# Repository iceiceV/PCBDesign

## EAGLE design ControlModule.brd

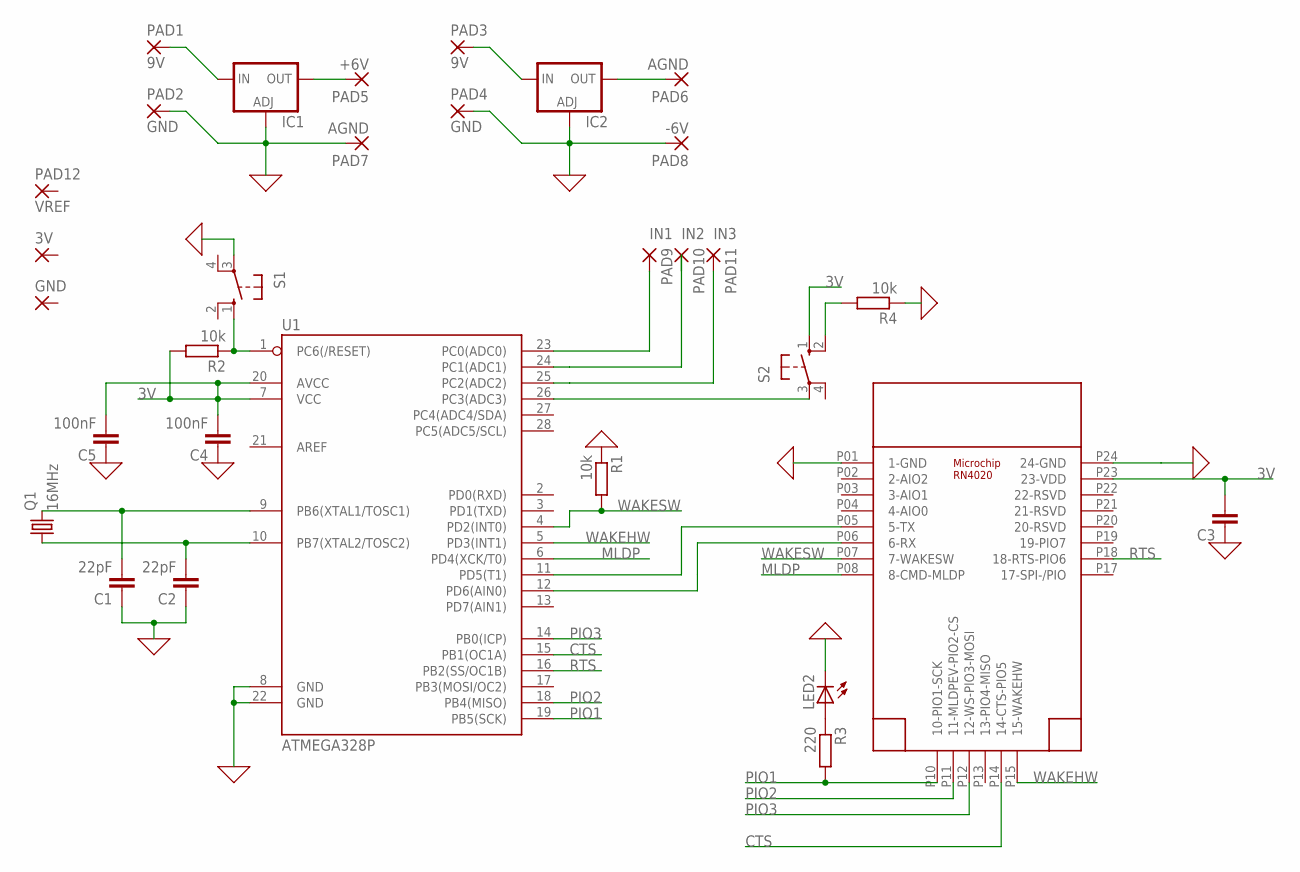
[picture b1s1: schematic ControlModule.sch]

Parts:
3V: 2,54/1,1
C1, C2: 22pF; C0603
C3: C-EUC0603; C0603
C4, C5: 100nF; C0603
GND: 2,54/1,1
IC1, IC2: LM138-TL; TO220L1
LED2: LEDCHIPLED_0603; CHIPLED_0603
PAD1, PAD3: 9V; 2,54/1,1
PAD2, PAD4: GND; 2,54/1,1
PAD5: +6V; 2,54/1,1
PAD6, PAD7: AGND; 2,54/1,1
PAD8: -6V; 2,54/1,1
PAD9, PAD10, PAD11: 2,54/1,1
PAD12: VREF; 2,54/1,1
Q1: 16MHz; HC49/S
R1, R2, R4: 10k; R0805
R3: 220; R0805
S1, S2: 10-XX; B3F-10XX
U1: ATMEGA328P; DIP28
U$1: RN4020; RN4020SMD

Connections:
0: C1.1, C2.1, C3.1, C4.1, C5.1, IC1.1 (ADJ), IC2.1 (ADJ), LED2.C, PAD2.1, PAD4.1, PAD7.1, PAD8.1, R1.1, R4.1, S1.3, U1.8 (GND), U1.22 (GND), U$1.P01 (1-GND), U$1.P24 (24-GND)
3V: C3.2, C4.2, C5.2, R2.2, S2.1 (S), U1.7 (VCC), U1.20 (AVCC), U$1.P23 (23-VDD)
9V: IC1.3 (IN), PAD1.1
CTS: U1.15 (PB1(OC1A)), U$1.P14 (14-CTS-PIO5)
IN1: PAD9.1, U1.23 (PC0(ADC0))
IN2: PAD10.1, U1.24 (PC1(ADC1))
IN3: PAD11.1, U1.25 (PC2(ADC2))
MLDP: U1.6 (PD4(XCK/T0)), U$1.P08 (8-CMD-MLDP)
unnamed: U1.12 (PD6(AIN0)), U$1.P06 (6-RX)
unnamed: U1.11 (PD5(T1)), U$1.P05 (5-TX)
unnamed: S2.3, U1.26 (PC3(ADC3))
unnamed: C1.2, Q1.2, U1.9 (PB6(XTAL1/TOSC1))
unnamed: IC2.3 (IN), PAD3.1
unnamed: IC1.2 (OUT), PAD5.1
unnamed: C2.2, Q1.1, U1.10 (PB7(XTAL2/TOSC2))
unnamed: IC2.2 (OUT), PAD6.1
unnamed: R2.1, S1.1 (S), U1.1 (PC6(/RESET))
unnamed: LED2.A, R3.1
unnamed: R4.2, S2.2 (S1)
PIO1: R3.2, U1.19 (PB5(SCK)), U$1.P10 (10-PIO1-SCK)
PIO2: U1.18 (PB4(MISO)), U$1.P11 (11-MLDPEV-PIO2-CS)
PIO3: U1.14 (PB0(ICP)), U$1.P12 (12-WS-PIO3-MOSI)
RTS: U1.16 (PB2(SS/OC1B)), U$1.P18 (18-RTS-PIO6)
WAKEHW: U1.5 (PD3(INT1)), U$1.P15 (15-WAKEHW)
WAKESW: R1.2, U1.4 (PD2(INT0)), U$1.P07 (7-WAKESW)

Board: 2 copper layers, 31 parts (0 on the bottom side), 25 nets, no tracks yet.

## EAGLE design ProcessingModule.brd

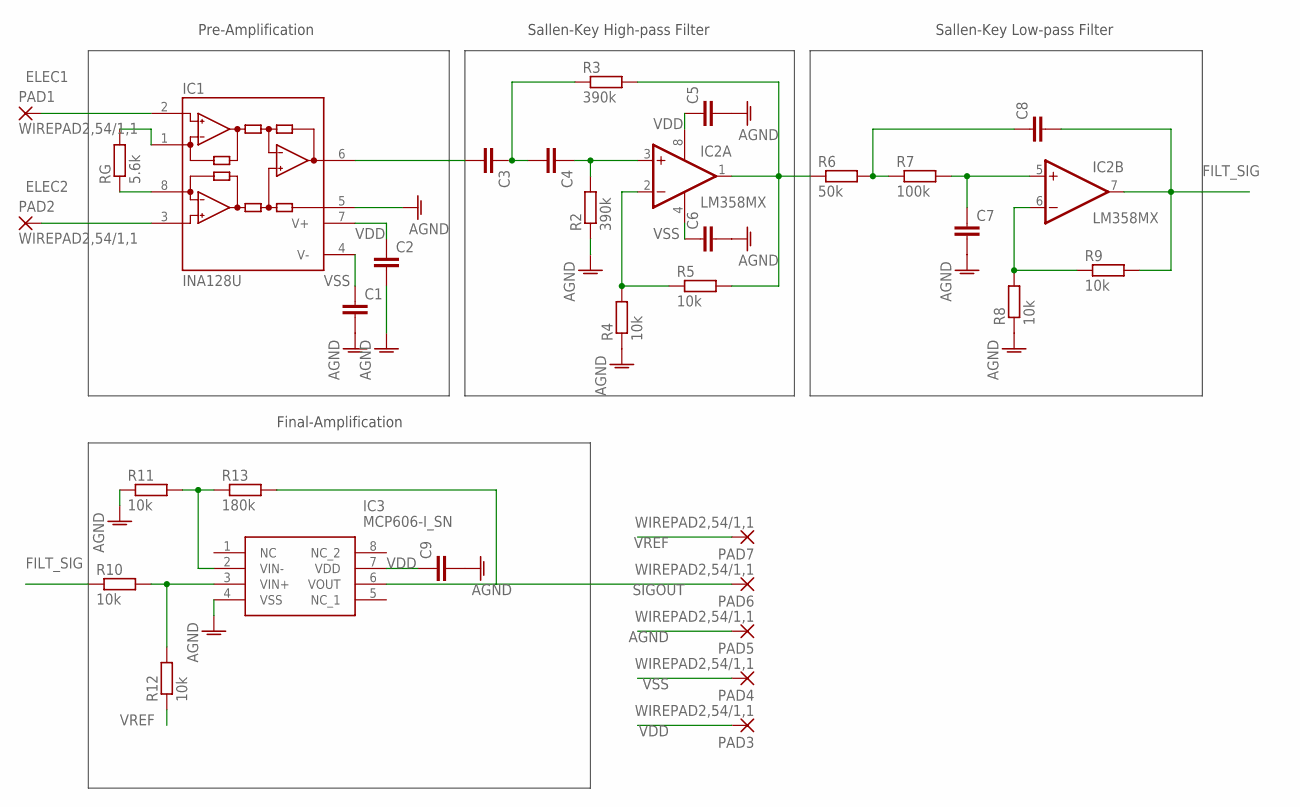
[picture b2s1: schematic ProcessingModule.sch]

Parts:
C1, C2, C3, C4, C5, C6, C7, C8, C9: C-EUC0603; C0603
IC1: INA128U; SO08
IC2: LM358MX; SO08
IC3: MCP606-I_SN; SOIC127P600X175-8N
PAD1, PAD2, PAD3, PAD4, PAD5, PAD6, PAD7: WIREPAD2,54/1,1; 2,54/1,1
R2, R3: 390k; R0805
R4, R5, R8, R9, R10, R11, R12: 10k; R0805
R6: 50k; R0805
R7: 100k; R0805
R13: 180k; R0805
RG: 5.6k; R0805

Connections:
AGND: C1.2, C2.2, C5.2, C6.2, C7.2, C9.2, IC1.5 (REF), IC3.4 (VSS), PAD5.1, R2.1, R4.1, R8.1, R11.1
ELEC1: IC1.2 (-IN), PAD1.1
ELEC2: IC1.3 (+IN), PAD2.1
FILT_SIG: C8.2, IC2.7 (OUT), R9.2, R10.1
unnamed: IC1.1 (RG), RG.2
unnamed: IC1.8 (RG), RG.1
unnamed: IC2.2 (-IN), R4.2, R5.1
unnamed 7: IC2.1 (OUT), R3.2, R5.2, R6.1; also elsewhere on the board
unnamed: C4.1, IC2.3 (+IN), R2.2
unnamed: C3.1, C4.2, R3.1
unnamed: C3.2, IC1.6 (OUT)
unnamed: C7.1, IC2.5 (+IN), R7.2
unnamed 12: C8.1, R6.2, R7.1; also elsewhere on the board
unnamed: IC3.3 (VIN+), R10.2, R12.2
unnamed: IC3.2 (VIN-), R11.2, R13.1
unnamed: IC2.6 (-IN), R8.2, R9.1
SIGOUT: IC3.6 (VOUT), PAD6.1, R13.2
VDD: C2.1, C5.1, C9.1, IC1.7 (V+), IC2.8 (V+), IC3.7 (VDD), PAD3.1
VREF: PAD7.1, R12.1
VSS: C1.1, C6.1, IC1.4 (V-), IC2.4 (V-), PAD4.1

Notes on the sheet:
Pre-Amplification
Sallen-Key High-pass Filter
Sallen-Key Low-pass Filter
Final-Amplification

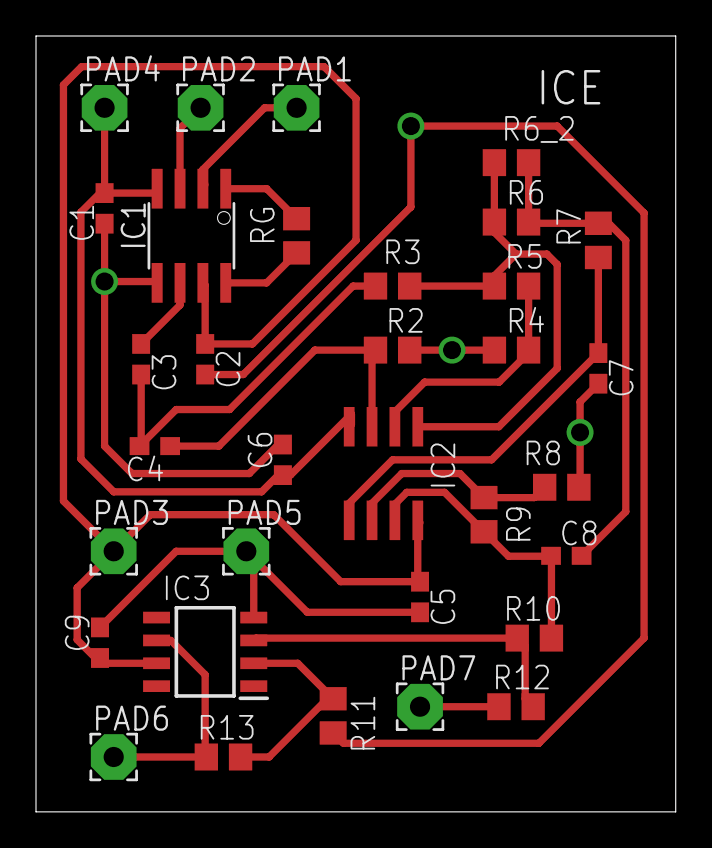
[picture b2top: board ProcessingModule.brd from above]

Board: 2 copper layers, 35.5 x 43.1 mm, 33 parts (0 on the bottom side), 20 nets.

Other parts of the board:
R6_2: 50k; R0805

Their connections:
unnamed 7: R6_2.1; also elsewhere on the board
unnamed 12: R6_2.2; also elsewhere on the board

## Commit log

2018-09-29 Started adding resistors for the amplification setup
2018-11-27 Final version for Processing Module
2018-11-28 drawing Control Module
2018-12-08 Control module first version and Processing module final design

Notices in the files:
parts and their libraries:
SparkFun-IC-Microcontroller: Licensing: Creative Commons ShareAlike 4.0 International - https://creativecommons.org/licenses/by-sa/4.0
